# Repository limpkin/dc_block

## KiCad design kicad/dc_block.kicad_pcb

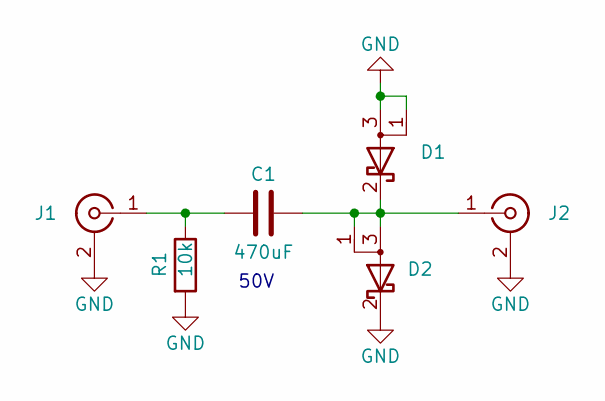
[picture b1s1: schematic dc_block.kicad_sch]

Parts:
C1: 470uF; CP_Radial_D16.0mm_P7.50mm
D1, D2: D_Schottky_AKA; CLA4607-085LF
J1, J2: COAX; SMA_ALIEXPRESS
R1: 10k; R_0805_2012Metric

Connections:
GND: D1.1 (A), D1.3 (A), D2.2 (K), J1.2 (Ext), J2.2 (Ext), R1.2
unnamed: C1.1, J1.1 (In), R1.1
unnamed: C1.2, D1.2 (K), D2.1 (A), D2.3 (A), J2.1 (In)

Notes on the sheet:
50V

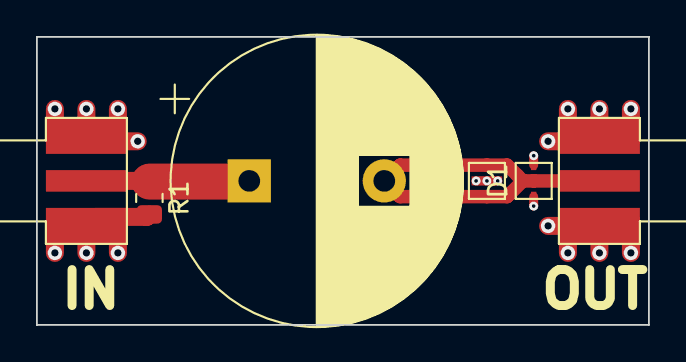
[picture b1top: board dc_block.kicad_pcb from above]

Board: 2 copper layers, 34.0 x 16.0 mm, 6 parts (0 on the bottom side), 3 nets.
